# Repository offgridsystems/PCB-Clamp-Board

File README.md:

# Clamp Board PCBs
### Hardware Files For both Dkblock Clamp Boards - 7.4V and 3.7V (one of each needed for each DKblock)
These are the printed circuit board (PCB) files, CAD files, specification sheets and all technical drawings needed to make each DKblock Clamp board. Note that the bill of materials (BOM) and other technical documents can be opened in [OpenOffice](https://www.openoffice.org) format and PCB files are in [EAGLE](https://www.autodesk.com/products/eagle/overview) format, but they can also be opened and edited in the open source Kicad program.
One version is provided for each board, Rev C are fully tested boards, put into limited production and used on a 72VDC electric scooter named Fido, and a 150VDC VW bug conversion, and other EV projects. 
Also note that the cells have 20 amp fuse protection on each cell. See "Blowup of trace fuse with comments.pdf" graphic

All DKblock software and hardware is released as open source hardware (OSHW) as defined by the OSHWA: https://www.oshwa.org/definition/ and under the JSON license defined at https://www.json.org/license.html

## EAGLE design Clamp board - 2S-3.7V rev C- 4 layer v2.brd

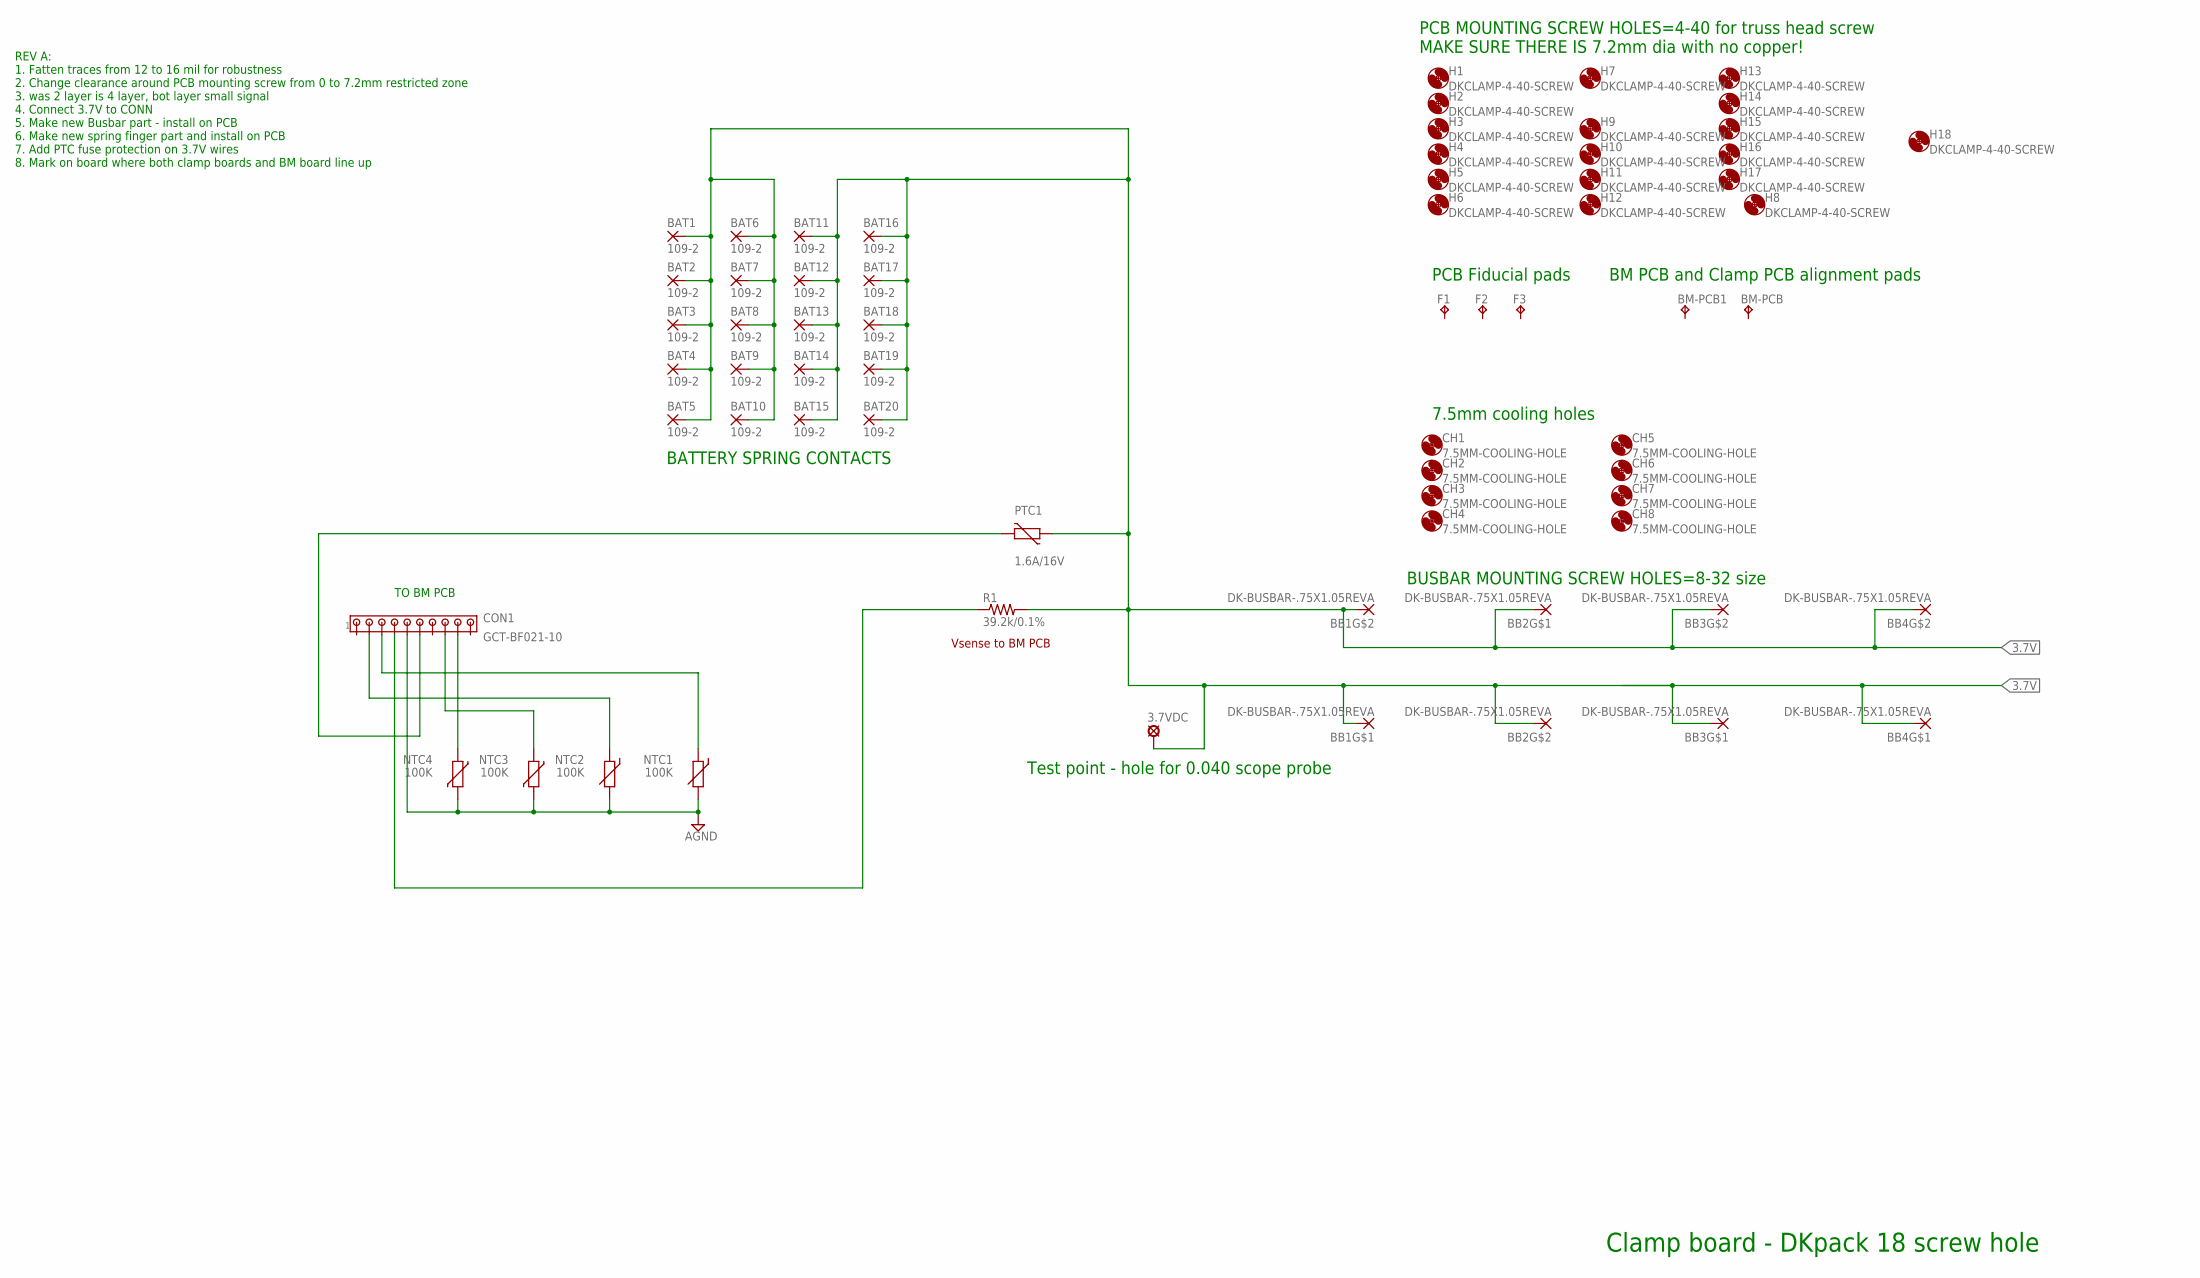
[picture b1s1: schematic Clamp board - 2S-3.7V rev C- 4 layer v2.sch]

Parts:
3.7VDC: LSP10
BAT1, BAT2, BAT3, BAT4, BAT5, BAT6, BAT7, BAT8, BAT9, BAT10, BAT11, BAT12, BAT13, BAT14, BAT15, BAT16, BAT17, BAT18, BAT19, BAT20: 109-2; DK-SPRING-FINGER-REV2
BB1, BB2, BB3, BB4: DK-BUSBAR-.75X1.05REVA; DKBUSBAR
BM-PCB, BM-PCB1: FIDUCIALTP15SQ; TP15SQ
CH1, CH2, CH3, CH4, CH5, CH6, CH7, CH8: 7.5MM-COOLING-HOLE
CON1: GCT-BF021-10
F1, F2, F3: FIDUCIALB1,27; B1,27
H1, H2, H3, H4, H5, H6, H7, H8, H9, H10, H11, H12, H13, H14, H15, H16, H17, H18: DKCLAMP-4-40-SCREW; 2.95MM-HOLE-FOR-4-40SCREW-DKCLAMP
NTC1, NTC2: 100K; 0603
NTC3, NTC4: 100K; VARISTOR_0603
PTC1: 1.6A/16V; CT/CN1812; MPN Bel 0ZCG0160BF2C
R1: 39.2k/0.1%; R0603

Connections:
3.7V: 3.7VDC.MP, BAT1.2, BAT2.2, BAT3.2, BAT4.2, BAT5.2, BAT6.2, BAT7.2, BAT8.2, BAT9.2, BAT10.2, BAT11.2, BAT12.2, BAT13.2, BAT14.2, BAT15.2, BAT16.2, BAT17.2, BAT18.2, BAT19.2, BAT20.2, BB1.P$2, BB1.P$3, BB2.P$2, BB2.P$3, BB3.P$2, BB3.P$3, BB4.P$2, BB4.P$3, PTC1.1, R1.2
3.7VPOWER: CON1.P$6 (6), PTC1.2
3.7VSCALED: CON1.P$4 (4), R1.1
AGND: CON1.P$5 (5), NTC1.2, NTC2.2, NTC3.2, NTC4.2
NTC1: CON1.P$3 (3), NTC1.1
NTC2: CON1.P$2 (2), NTC2.1
NTC3: CON1.P$8 (8), NTC3.1
NTC4: CON1.P$9 (9), NTC4.1

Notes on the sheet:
Clamp board - DKpack 18 screw hole
PCB MOUNTING SCREW HOLES=4-40 for truss head screw MAKE SURE THERE IS 7.2mm dia with no copper!
BATTERY SPRING CONTACTS
PCB Fiducial pads
7.5mm cooling holes
Test point - hole for 0.040 scope probe
TO BM PCB
BUSBAR MOUNTING SCREW HOLES=8-32 size
Vsense to BM PCB
REV A: 1. Fatten traces from 12 to 16 mil for robustness 2. Change clearance around PCB mounting screw from 0 to 7.2mm restricted zone 3. was 2 layer is 4 layer, bot layer small signal 4. Connect 3.7V to CONN 5. Make new Busbar part - install on PCB 6. Make new spring finger part and install on PCB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
BM PCB and Clamp PCB alignment pads

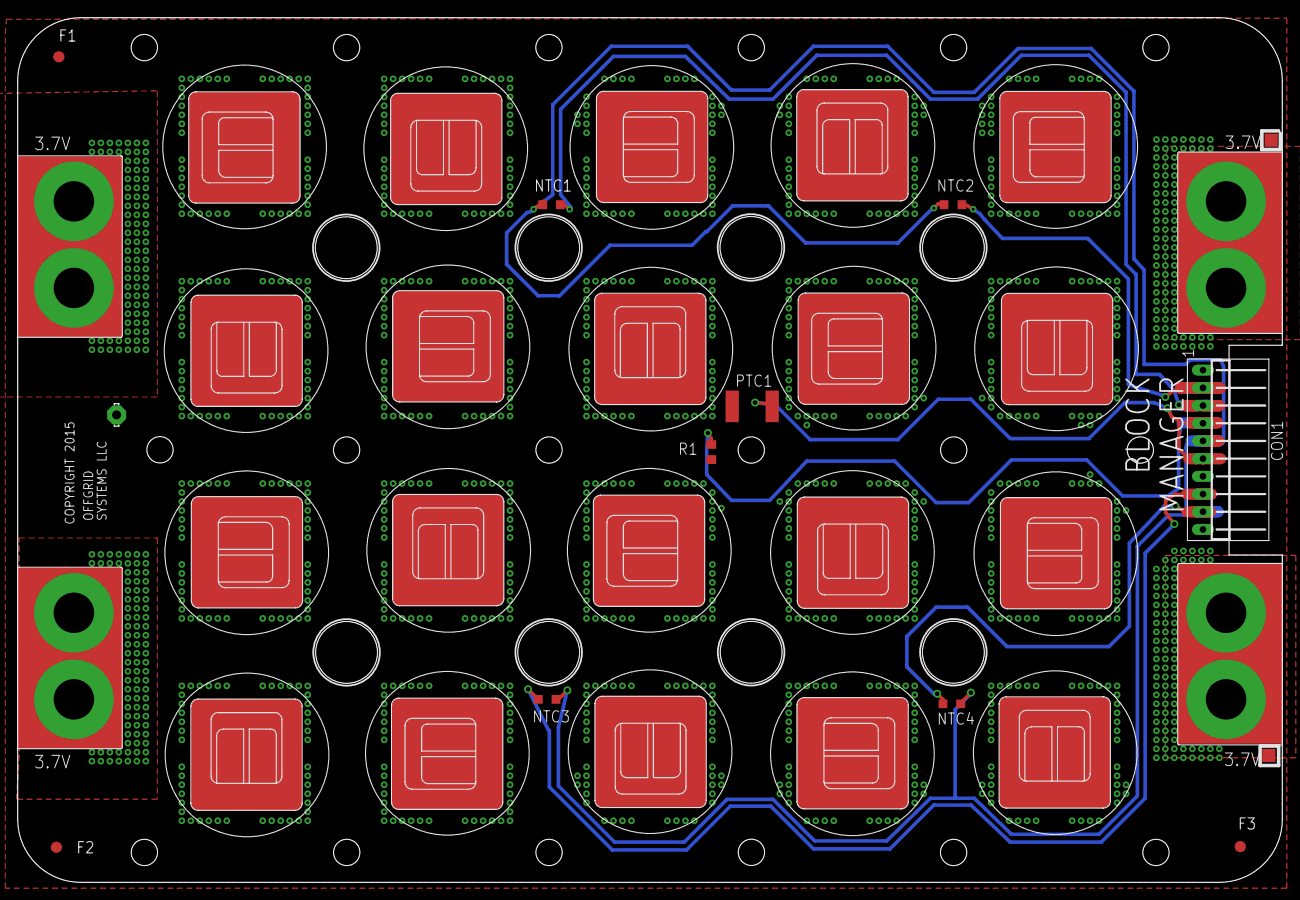
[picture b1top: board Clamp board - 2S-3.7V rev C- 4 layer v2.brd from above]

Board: 4 copper layers, 142.9 x 97.7 mm, 63 parts (0 on the bottom side), 8 nets.

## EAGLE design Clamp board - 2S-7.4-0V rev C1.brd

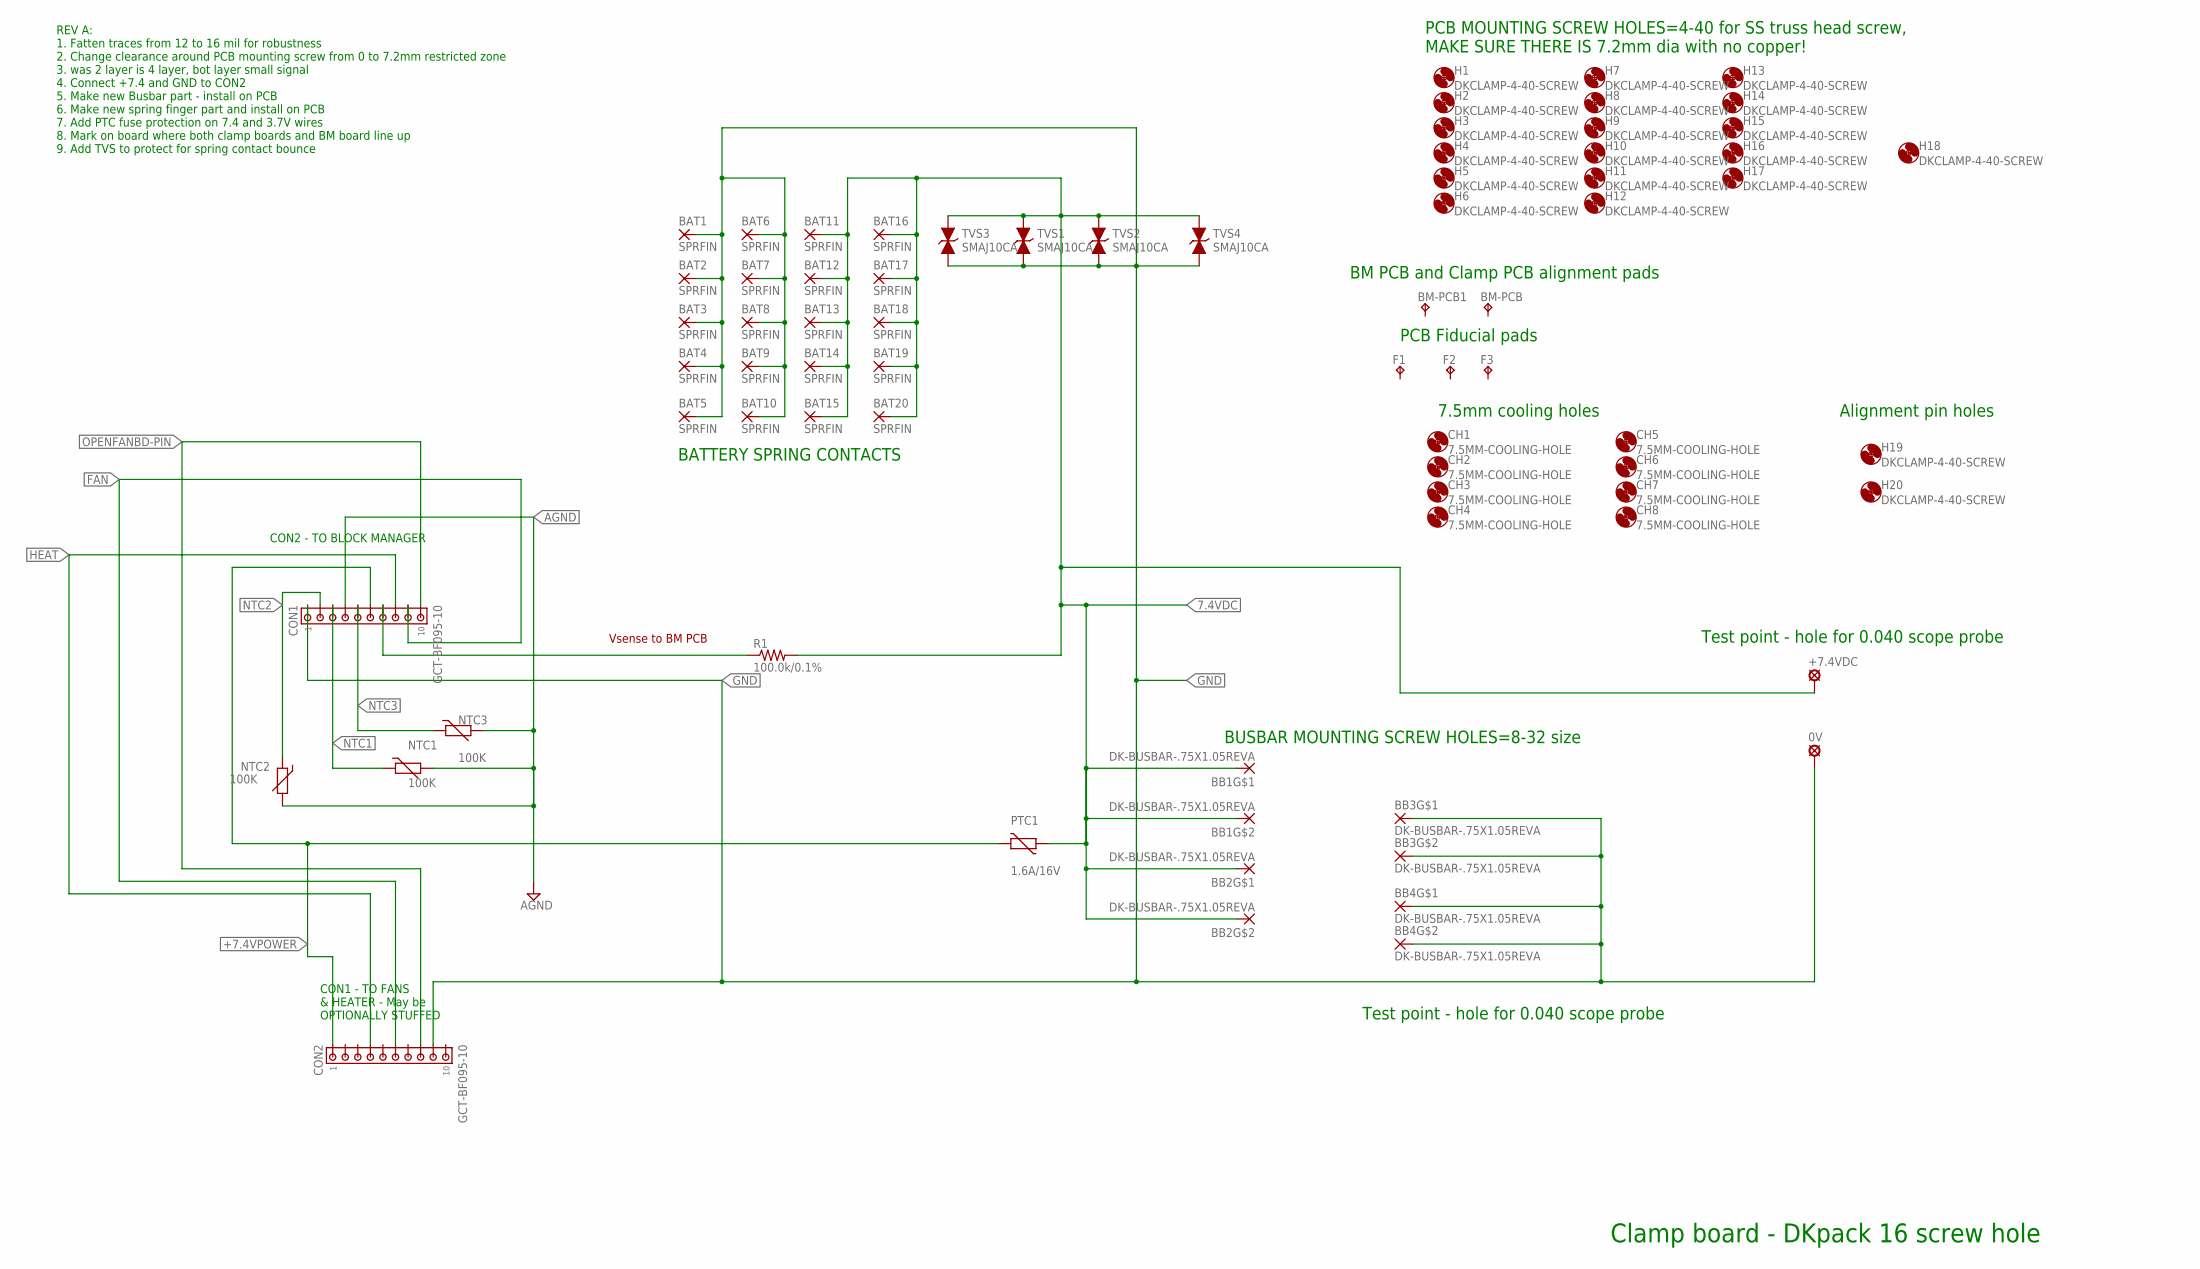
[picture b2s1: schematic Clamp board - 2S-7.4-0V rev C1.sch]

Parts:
0V: LSP10
+7.4VDC: LSP10
BAT1: SPRFIN; DK-SPRING-FINGER-REV2; MPN Keystone 109-2
BAT2, BAT3, BAT4, BAT5, BAT6, BAT7, BAT8, BAT9, BAT10, BAT11, BAT12, BAT13, BAT14, BAT15, BAT16, BAT17, BAT18, BAT19, BAT20: SPRFIN; DK-SPRING-FINGER-REV2
BB1, BB2, BB3, BB4: DK-BUSBAR-.75X1.05REVA; DKBUSBAR
BM-PCB, BM-PCB1: FIDUCIALTP15SQ; TP15SQ
CH1, CH2, CH3, CH4, CH5, CH6, CH7, CH8: 7.5MM-COOLING-HOLE
CON1, CON2: GCT-BF095-10; GCT-BF085-10
F1, F2, F3: FIDUCIALB1,27; B1,27
H1, H2, H3, H4, H5, H6, H7, H8, H9, H10, H11, H12, H13, H14, H15, H16, H17, H18, H19, H20: DKCLAMP-4-40-SCREW; 2.95MM-HOLE-FOR-4-40SCREW-DKCLAMP
NTC1, NTC2, NTC3: 100K; 0603; MPN MURATA NCP18WF104J03RB
PTC1: 1.6A/16V; CT/CN1812; MPN Bel 0ZCG0160BF2C
R1: 100.0k/0.1%; R0603
TVS1, TVS2, TVS3, TVS4: SMAJ10CA; SMAJ; MPN ST SMAJ10CA-TR

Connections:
7.4VDC: +7.4VDC.MP, BAT11.2, BAT12.2, BAT13.2, BAT14.2, BAT15.2, BAT16.2, BAT17.2, BAT18.2, BAT19.2, BAT20.2, BB1.P$2, BB1.P$3, BB2.P$2, BB2.P$3, PTC1.1, R1.2, TVS1.K (C), TVS2.K (C), TVS3.K (C), TVS4.K (C)
7.4VSCALED: CON1.P$7 (7), R1.1
+7.4VPOWER: CON1.P$6 (6), CON2.P$1 (1), PTC1.2
AGND: CON1.P$4 (4), NTC1.2, NTC2.2, NTC3.2
FAN: CON1.P$9 (9), CON2.P$6 (6)
GND: 0V.MP, BAT1.2, BAT2.2, BAT3.2, BAT4.2, BAT5.2, BAT6.2, BAT7.2, BAT8.2, BAT9.2, BAT10.2, BB3.P$2, BB3.P$3, BB4.P$2, BB4.P$3, CON1.P$1 (1), CON2.P$9 (9), TVS1.A, TVS2.A, TVS3.A, TVS4.A
HEAT: CON1.P$8 (8), CON2.P$4 (4)
NTC1: CON1.P$3 (3), NTC1.1
NTC2: CON1.P$2 (2), NTC2.1
NTC3: CON1.P$5 (5), NTC3.1
OPENFANBD-PIN: CON1.P$10 (10), CON2.P$8 (8)

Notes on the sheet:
Clamp board - DKpack 16 screw hole
PCB MOUNTING SCREW HOLES=4-40 for SS truss head screw, MAKE SURE THERE IS 7.2mm dia with no copper!
BATTERY SPRING CONTACTS
PCB Fiducial pads
7.5mm cooling holes
BUSBAR MOUNTING SCREW HOLES=8-32 size
Test point - hole for 0.040 scope probe
CON1 - TO FANS & HEATER - May be OPTIONALLY STUFFED
CON2 - TO BLOCK MANAGER
REV A: 1. Fatten traces from 12 to 16 mil for robustness 2. Change clearance around PCB mounting screw from 0 to 7.2mm restricted zone 3. was 2 layer is 4 layer, bot layer small signal 4. Connect +7.4 and GND to CON2 5. Make new Busbar part - install on PCB 6. Make new spring finger part and instal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
Vsense to BM PCB
BM PCB and Clamp PCB alignment pads
Alignment pin holes

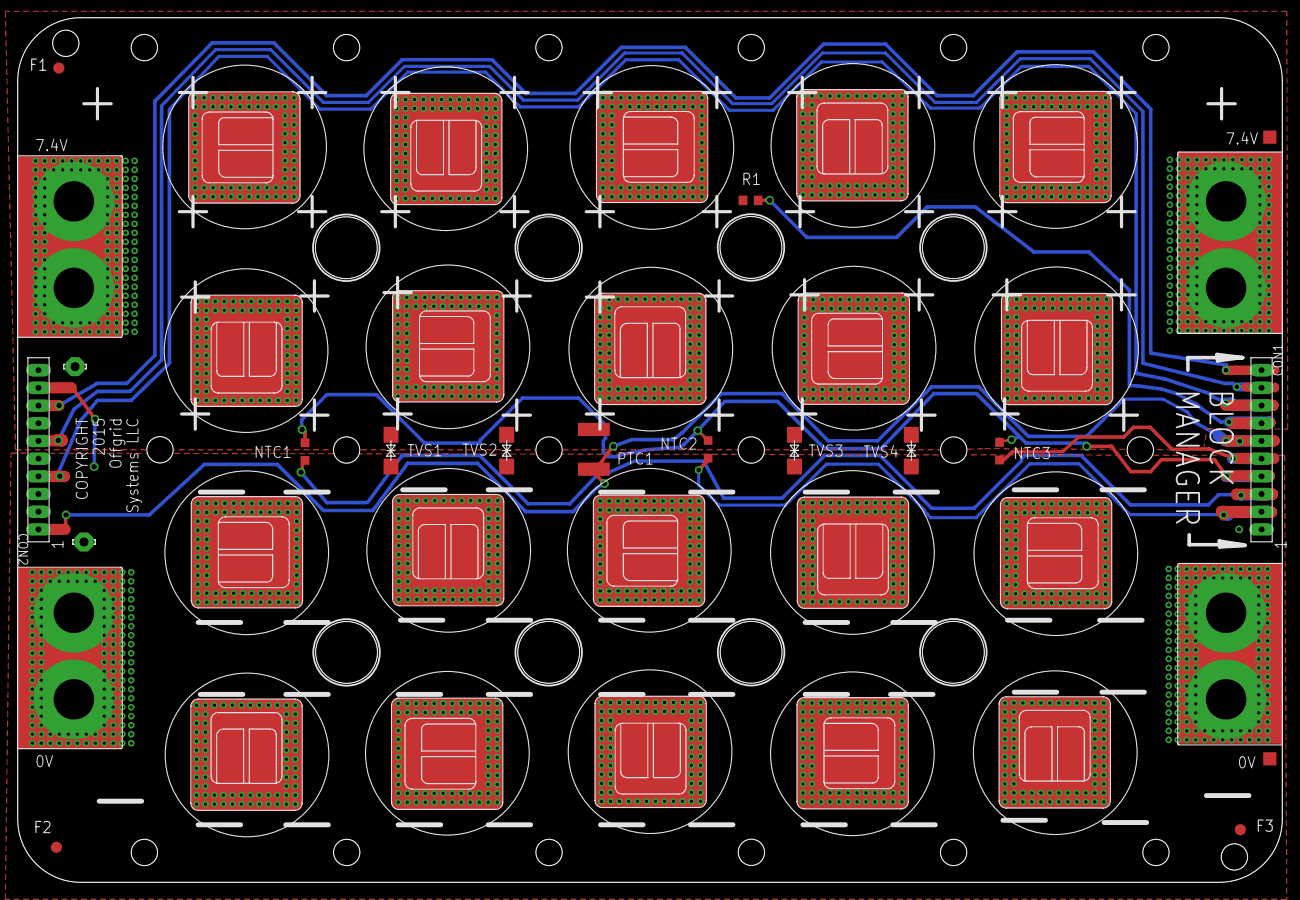
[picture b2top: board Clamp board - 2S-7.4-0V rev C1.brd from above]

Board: 4 copper layers, 142.9 x 97.7 mm, 70 parts (0 on the bottom side), 11 nets.

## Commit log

2019-11-22 Major Push
2020-02-05 Hole alignment fix (until next revision)
2020-03-16 kicad update

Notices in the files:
Clamp board - 2S-3.7V rev C- 4 layer v2.brd:
COPYRIGHT 2015
